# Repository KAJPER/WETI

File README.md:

# Bezkontaktowy miernik odległości (ultradźwiękowy)

Miernik odległości na mikrokontrolerze **ATtiny1616**, mierzący dystans do obiektu
ultradźwiękami **40 kHz** w zakresie **10–50 cm**. Projekt na ogólnopolski konkurs
**„Wygraj Indeks WETI 2026"** (Politechnika Gdańska).

Metoda hybrydowa **Pulse-Phase Ranging**: zgrubny pomiar czasu przelotu (ToF) z obwiedni
echa + docinanie fazą nośnej (filtr Goertzela), z kompensacją temperatury termistorem NTC.
Firmware napisany **w czystym AVR-GCC, na rejestrach (bez Arduino)**.

## Parametry (zmierzone)

| Parametr | Wartość |
|---|---|
| Zakres pomiaru | 10–50 cm (karton 20×20 cm) |
| Błąd RMSE | **≈ 2,4 mm** (35 odczytów, kalibracja liniowa) |
| Pobór mocy (spoczynek) | **0,18 mA @ 5 V = 0,9 mW** |
| Koszt elementów | 43,73 PLN |
| Zasilanie | 5 V (LDO MCP1700 → 3,3 V) |
| Zegar | 10 MHz (wewn. OSC20M / 2) |

## Jak to działa

1. **Nadawanie** — mikrokontroler generuje paczkę 40 kHz (dokładny rezonans przetwornika)
   na pinie PB0, wzmacnianą tranzystorem BC817.
2. **Odbiór** — echo wzmacnia dwustopniowy tor na MCP6002 (filtr pasmowy ~40 kHz),
   bramkowany P-MOSFET-em (BSS84) dla oszczędności energii.
3. **ToF** — ADC szybko próbkuje obwiednię echa (8-bit, ~115 ksps); początek echa
   (*onset*, próg 40 % szczytu z interpolacją) daje czas przelotu mierzony licznikiem
   TCB0 (100 ns/takt). Seria 9 strzałów → mediana + odrzucanie outlierów (MAD).
4. **Faza** — filtr Goertzela na buforze próbek wyznacza fazę nośnej (uśrednianą po
   pingach, z miarą spójności PLV) do dociągnięcia wyniku do siatki λ/2 ≈ 4,3 mm.
5. **Temperatura** — NTC 10 kΩ (model Beta) koryguje prędkość dźwięku c(T) = 331,3 + 0,606·T.
6. **Energia** — między pomiarami MCU śpi w trybie Standby, budzony z RTC/PIT;
   tor analogowy zasilany tylko na czas pomiaru.

Dostępna jest też **2-punktowa kalibracja polowa** zapisywana w EEPROM (wejście:
przytrzymanie przycisku przy starcie).

## Struktura repozytorium

| Katalog / plik | Zawartość |
|---|---|
| `firmware/` | Kod źródłowy (`main.c`), plik wynikowy (`main.hex`), `Makefile` |
| `dokumentacja-etap2/` | Dokumentacja prototypu (LaTeX + PDF), zdjęcia w `foto/` |
| `dokumentacja-etap1/` | Projekt koncepcyjny (teza, schemat, PCB, symulacje LTspice) |
| `deliverables/` | Paczka konkursowa (firmware, CAD, Gerber) |
| `obudowa/` | Modele obudowy (druk 3D) |
| `WETI_Kacper_Popko_Etap2.zip` | Gotowa paczka do oddania |

## Budowanie i wgranie firmware

Wymagane: `avr-gcc`, `avrdude`, programator UPDI (np. SerialUPDI / CP2102 albo
Arduino z jtag2updi).

```bash
cd firmware
make
avrdude -c jtag2updi -p attiny1616 -P COMx -b 115200 -U flash:w:main.hex:i
```

Wynik pomiaru wychodzi przez USART (pin PB2, 115200 8N1):
```
#1 D=203mm (Dc=204 ph=240.5 plv=98 T=22.6C 9/9 pk=18)
```
`D` — odległość po fuzji fazowej, `Dc` — zgrubna (ToF), `ph` — faza, `plv` — spójność
fazy, `T` — temperatura, `pk` — amplituda echa.

## Sprzęt

ATtiny1616-SN · MCP6002 (wzmacniacz) · MCP1700 (LDO 3,3 V) · BC817 (driver TX) ·
BSS84 (bramkowanie toru) · NTC 10 kΩ · para przetworników US 40 kHz · PCB 2-warstwowe 41 × 54,25 mm.

## Autor

Kacper Popko — projekt konkursowy „Wygraj Indeks WETI 2026".

## Licencja

© 2026 Kacper Popko. Projekt (sprzęt, oprogramowanie, dokumentacja) jest
**open source** na licencji
**[CC BY-NC-SA 4.0](https://creativecommons.org/licenses/by-nc-sa/4.0/deed.pl)**:

- ✅ możesz **kopiować, używać i edytować / rozwijać** projekt,
- ✏️ przeróbki musisz udostępniać **na tej samej licencji** (SA),
- 👤 musisz **podać autora** (Kacper Popko) (BY),
- 🚫 **nie wolno wykorzystywać komercyjnie** — w tym sprzedawać urządzenia,
  płytek, oprogramowania ani odpłatnych usług (NC).

Szczegóły w pliku [`LICENSE`](LICENSE).

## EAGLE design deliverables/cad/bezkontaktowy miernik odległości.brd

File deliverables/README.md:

# WETI 2026 — Etap 2: paczka dla Komisji

Termin: **19.06.2026, 15:00**. Poniżej checklista wymaganych plików i co już jest gotowe.

## Wymagane elementy (z regulaminu Etapu 2)

| # | Element | Status | Lokalizacja |
|---|---------|--------|-------------|
| 1 | Prototyp urządzenia (fizyczny) | ✅ zbudowany, działa | — (sprzęt) |
| 2 | Pliki produkcyjne PCB — **Gerber** | ✅ dodane (zip, v17) | `gerber/` |
| 3 | Pliki źródłowe CAD — schemat + PCB | ✅ dodane (.sch + .brd) | `cad/` |
| 4 | Oprogramowanie — źródło + plik końcowy | ✅ gotowe | `firmware/` |
| 5 | Dokumentacja | ✅ gotowa | `../dokumentacja-etap2/` |

Gerber (zip) zawiera komplet warstw: copper top/bottom, soldermask, silkscreen,
solderpaste, profil (obrys), drill (.xln) oraz pliki PnP/assembly — gotowe do
produkcji. CAD: `bezkontaktowy_miernik_odległości.sch` + `...brd` (EAGLE).

## 2 + 3: Referencja eksportu (zrobione)

Poniższa instrukcja pozostaje jako referencja, gdyby trzeba było wygenerować
Gerbery ponownie po zmianie PCB.

### Skopiuj źródła CAD → `cad/`
- `WETI.sch` (schemat)
- `WETI.brd` (płytka)

### Wyeksportuj Gerber → `gerber/` (EAGLE: File → CAM Processor)
Użyj wbudowanego job `gerber_2-layer` (albo `gerb274x`) i wygeneruj warstwy:

| Plik | Warstwa EAGLE | Opis |
|------|---------------|------|
| `*.GTL` | Top | miedź górna |
| `*.GBL` | Bottom | miedź dolna |
| `*.GTS` | tStop | soldermask górny |
| `*.GBS` | bStop | soldermask dolny |
| `*.GTO` | tPlace + tNames | opis górny (silk) |
| `*.GBO` | bPlace + bNames | opis dolny (silk) |
| `*.GTP` | tCream | pasta górna (opcjonalnie) |
| `*.GKO` / `*.GML` | Dimension | obrys płytki |
| `*.TXT` / `*.XLN` | Drill (Excellon) | otwory |

Po eksporcie sprawdź wynik w darmowym wieweru Gerber (np. **gerbv** albo
**JLCPCB/Aisler online viewer**) — czy warstwy się pokrywają i obrys jest zamknięty.

## 4: Oprogramowanie — gotowe ✅

W katalogu `../firmware/`:
- `main.c` — kod źródłowy (AVR-GCC, rejestrowo, ATtiny1616)
- `main.hex` — plik wynikowy (Intel HEX) do wgrania
- `Makefile` — budowanie i programowanie

Budowanie i wgranie:
```
cd firmware
make
avrdude -c jtag2updi -p attiny1616 -P COM5 -b 115200 -U flash:w:main.hex:i
```
(lub `-c serialupdi` dla programatora SerialUPDI/CP2102)

## 5: Dokumentacja — gotowa ✅

`../dokumentacja-etap2/WETI_Kacper_Popko_Etap2.tex` (+ skompilowany `.pdf`).

## Przed wysłaniem — checklista końcowa
- [ ] `cad/WETI.sch` i `cad/WETI.brd` wgrane
- [ ] `gerber/` zawiera wszystkie warstwy + drill, sprawdzone w viewerze
- [ ] `firmware/main.hex` aktualny (po `make`)
- [ ] `dokumentacja-etap2/*.pdf` skompilowany
- [ ] zdjęcia/rendery prototypu dołączone

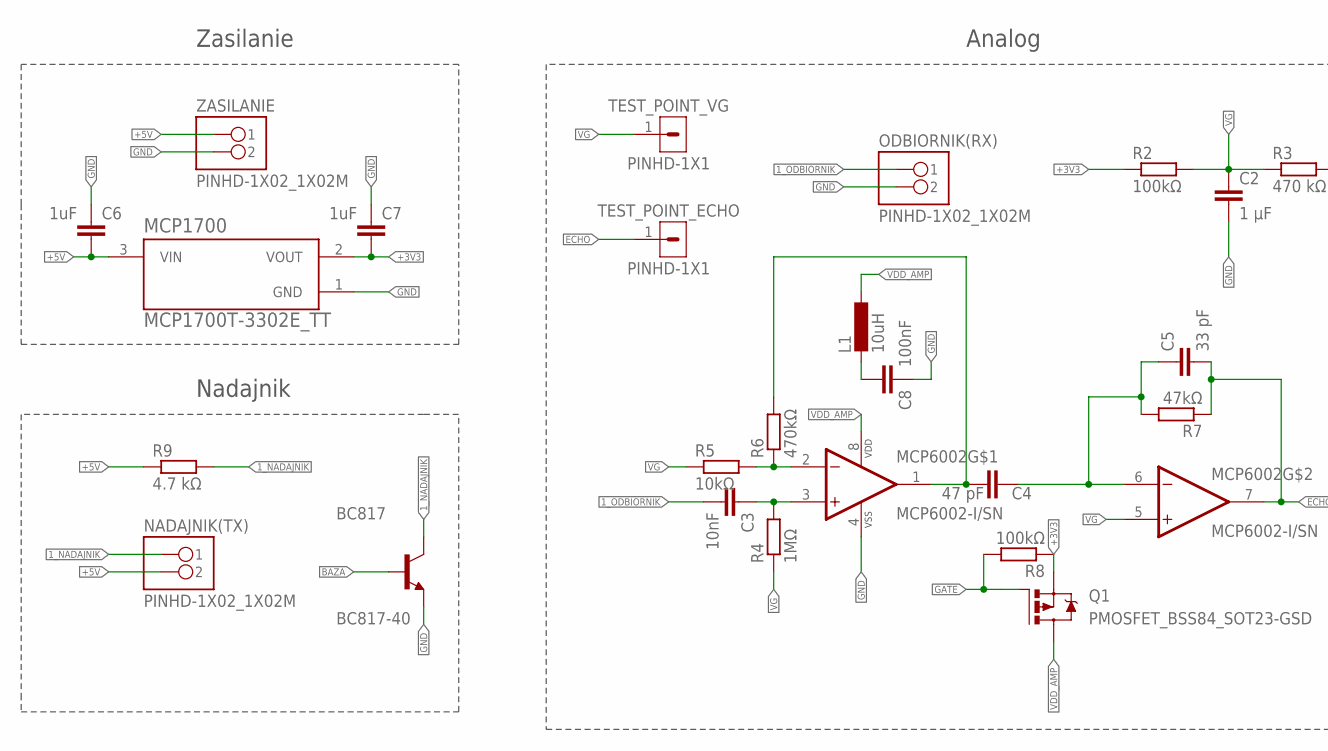
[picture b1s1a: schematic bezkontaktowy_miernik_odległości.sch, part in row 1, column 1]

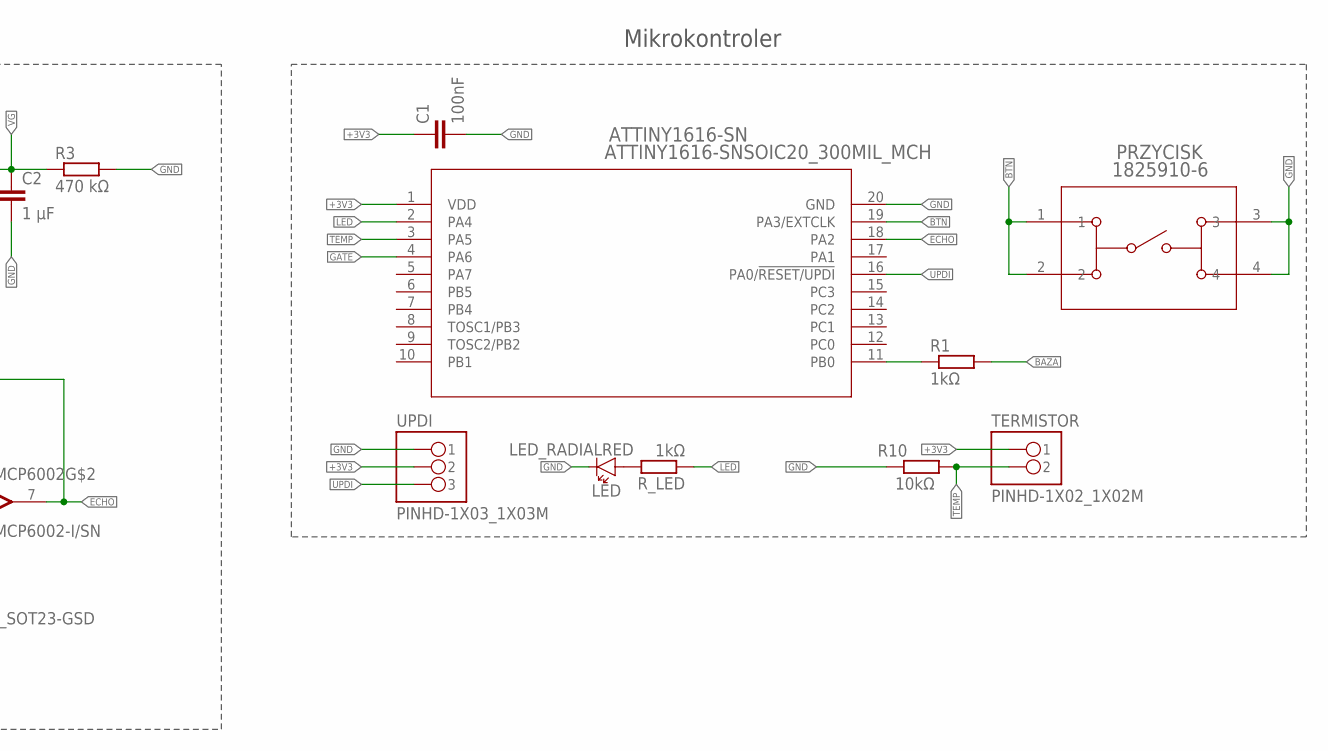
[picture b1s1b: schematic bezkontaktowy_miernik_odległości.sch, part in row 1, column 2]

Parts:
ATTINY1616-SN: ATTINY1616-SNSOIC20_300MIL_MCH; SOIC20_300MIL_MCH
BC817: BC817-40; SOT95P240X120-3N
C1, C8: 100nF; C0603
C2: 1 µF; C0603
C3: 10nF; C0603
C4: 47 pF; C0603
C5: 33 pF; C0603
C6, C7: 1uF; C0603
L1: 10uH; 0204/7
LED: LED_RADIALRED; LEDRD254W60D565H860B_R
MCP1700: MCP1700T-3302E_TT; SOT95P237X112-3N
MCP6002: MCP6002-I/SN; SOIC127P600X175-8N
NADAJNIK(TX): PINHD-1X02_1X02M; 1X02
ODBIORNIK(RX): PINHD-1X02_1X02M; 1X02
PRZYCISK: 1825910-6; SW4_1825910-B
Q1: PMOSFET_BSS84_SOT23-GSD; SOT23
R1: 1kΩ; R0603
R2, R8: 100kΩ; R0603
R3: 470 kΩ; R0603
R4: 1MΩ; R0603
R5, R10: 10kΩ; R0603
R6: 470kΩ; R0603
R7: 47kΩ; R0603
R9: 4.7 kΩ; R0603
R_LED: 1kΩ; R0603
TERMISTOR: PINHD-1X02_1X02M; 1X02
TEST_POINT_ECHO: PINHD-1X1; 1X01
TEST_POINT_VG: PINHD-1X1; 1X01
UPDI: PINHD-1X03_1X03M; 1X03
ZASILANIE: PINHD-1X02_1X02M; 1X02

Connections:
1_NADAJNIK: BC817.3 (C), NADAJNIK(TX).1, R9.2
1_ODBIORNIK: C3.2, ODBIORNIK(RX).1
+3V3: ATTINY1616-SN.1 (VDD), C1.1, C7.2, MCP1700.2 (VOUT), Q1.2 (S), R2.1, R8.1, TERMISTOR.1, UPDI.2
+5V: C6.2, MCP1700.3 (VIN), NADAJNIK(TX).2, R9.1, ZASILANIE.1
BAZA: BC817.1 (B), R1.2
BTN: ATTINY1616-SN.19 (PA3/EXTCLK), PRZYCISK.1, PRZYCISK.2
ECHO: ATTINY1616-SN.18 (PA2), C5.2, MCP6002.7 (VOUTB), R7.1, TEST_POINT_ECHO.1
GATE: ATTINY1616-SN.4 (PA6), Q1.1 (G), R8.2
GND: ATTINY1616-SN.20 (GND), BC817.2 (E), C1.2, C2.2, C6.1, C7.1, C8.1, LED.C, MCP1700.1 (GND), MCP6002.4 (VSS), ODBIORNIK(RX).2, PRZYCISK.3, PRZYCISK.4, R3.2, R10.1, UPDI.1, ZASILANIE.2
LED: ATTINY1616-SN.2 (PA4), R_LED.1
unnamed: C3.1, MCP6002.3 (VINA+), R4.2
unnamed: MCP6002.2 (VINA-), R5.2, R6.1
unnamed: C4.2, MCP6002.1 (VOUTA), R6.2
unnamed: LED.A, R_LED.2
unnamed: C4.1, C5.1, MCP6002.6 (VINB-), R7.2
unnamed: C8.2, L1.2
unnamed: ATTINY1616-SN.11 (PB0), R1.1
TEMP: ATTINY1616-SN.3 (PA5), R10.2, TERMISTOR.2
UPDI: ATTINY1616-SN.16 (PA0/!RESET/UPDI), UPDI.3
VDD_AMP: L1.1, MCP6002.8 (VDD), Q1.3 (D)
VG: C2.1, MCP6002.5 (VINB+), R2.2, R3.1, R4.1, R5.1, TEST_POINT_VG.1

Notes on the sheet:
Zasilanie
Nadajnik
Analog
Mikrokontroler

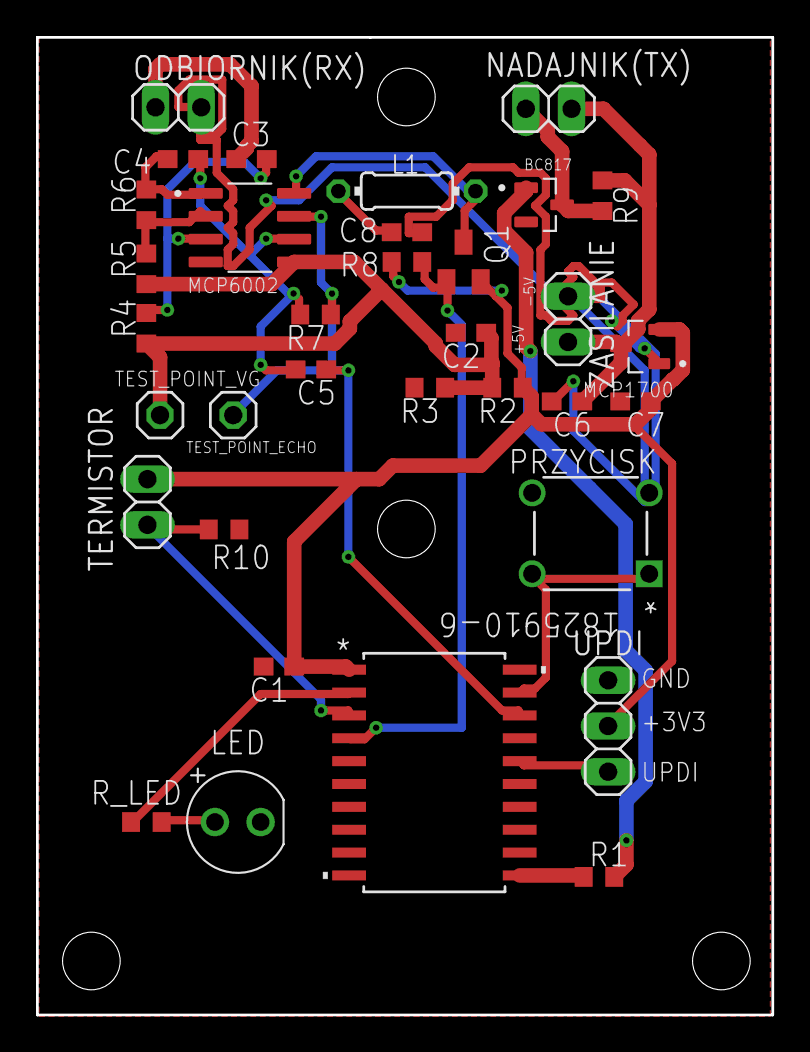
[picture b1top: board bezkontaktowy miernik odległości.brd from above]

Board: 2 copper layers, 40.9 x 54.3 mm, 34 parts (0 on the bottom side), 21 nets.

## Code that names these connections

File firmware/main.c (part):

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 * ATtiny1616 ultrasonic distance meter — v2 hardware echo capture.
 *
 * Pinout (after PCB mod):
 *   PA0  UPDI
 *   PA1  -                (free, was wrongly assumed ECHO earlier)
 *   PA2  -                (free, was ADC ECHO before PCB mod)
 *   PA3  BTN              (pull-up, active LOW, BOTHEDGES wake)
 *   PA4  LED              (active HIGH)
 *   PA5  TEMP NTC         (ADC0 AIN5)
 *   PA6  GATE Q1          (LOW = Q1 ON = op-amp powered)
 *   PB0  BAZA TX          (40 kHz software bitbang)
 *   PB2  USART0 TXD       (115200 8N1)
 *   PB4  ECHO             (AC1 AINP3 — hardware capture path)
 *
 * Detection chain (zero CPU latency):
 *   echo → op-amp → PB4 → AC1 (vs DAC1 threshold) → EVSYS → TCB0.CAPT
 *   NOTE: PB4 is AINP3 on AC1 (positive); on AC0 it is AINN1 (negative).
 * TCB0 latches CCMP exactly when AC0 toggles, no software loop needed.
 * 1 tick @ F_CPU=10 MHz = 100 ns; 16-bit counter = max 6.55 ms = 1.12 m.
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/* ============================== GPIO ================================== */
static void gpio_init(void)
{
    /* PA3 button with pull-up + BOTHEDGES IRQ (IDLE wake) */
    PORTA.DIRCLR   = PIN3_bm;
    PORTA.PIN3CTRL = PORT_PULLUPEN_bm | PORT_ISC_BOTHEDGES_gc;

    /* PA4 LED */
    PORTA.DIRSET = PIN4_bm; PORTA.OUTCLR = PIN4_bm;

    /* PA5 NTC analog input */
    PORTA.DIRCLR   = PIN5_bm;
    PORTA.PIN5CTRL = PORT_ISC_INPUT_DISABLE_gc;

    /* PA6 GATE Q1 — DIAGNOSTIC: Q1 ALWAYS ON so PB4 can be measured stably */
    PORTA.DIRSET = PIN6_bm; PORTA.OUTCLR = PIN6_bm;

    /* PB0 TX burst output */
    PORTB.DIRSET = PIN0_bm; PORTB.OUTCLR = PIN0_bm;

    /* PB2 USART TX */
    PORTB.DIRSET = PIN2_bm; PORTB.OUTSET = PIN2_bm;

    /* PB4 ECHO input for AC0 — disable digital, no pull */
    PORTB.DIRCLR   = PIN4_bm;
    PORTB.PIN4CTRL = PORT_ISC_INPUT_DISABLE_gc;

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}

/* ============================== NTC =================================== */
/* Topology: +3V3 -- NTC -- PA5 -- R10(10k) -- GND */
static int16_t ntc_read_temp_c16(void)
{
    uint16_t a = adc_read(ADC_MUXPOS_AIN5_gc);
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/* ============================== AC0 + DAC0 ============================ */
/* DAC0 generates threshold internally (no pin output).
 * CRITICAL (verified datasheet Table 5-1): on AC0, PB4 = AINN1 (NEGATIVE);
 * PB4 = AINP3 (positive) ONLY on AC1. So we MUST use AC1 for echo on PB4.
 * Datasheet 29.x: "AC1 uses DAC1" — threshold comes from DAC1, ref via
 * VREF.CTRLC (DAC1REFSEL) + VREF.CTRLB (DAC1REFEN, bit3).
 * AC1 compares PB4 (AINP3) vs DAC1; AC1_OUT → EVSYS → TCB0 capture. */
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
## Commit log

2026-05-13 Add initial firmware binary for test_pb0
    This commit introduces the firmware binary file `test_pb0.hex`, which contains the necessary machine code for the initial testing phase. The hex file includes a series of instructions and data requir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
2026-06-09 Add initial documentation for stage 1 in PDF format
2026-06-11 Add ESP32 power monitor and I2C scanner sketches
    - Implemented a power monitor for the WETI ultrasonic distance meter using INA219, featuring a web dashboard for live current, voltage, and power readings.
    - Added an I2C scanner sketch to identify connected I2C devices and their addresses.
2026-06-11 Add documentation for Stage 2 of the ultrasonic distance meter project
    - Created a new LaTeX document for Stage 2 documentation detailing the prototype's design, architecture, and performance.
    - Included sections on the introduction, requirements fulfillment, device architecture, firmware details, power management, measurement results, changes from Stage 1, deliverables, and future develop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
    - Added a table of contents for easy navigation within the document.
2026-06-11 Refactor code structure for improved readability and maintainability
2026-06-13 Add measurement characteristics and residual analysis plots to documentation
    - Included a new figure displaying the measurement characteristics after calibration, showing the correlation between actual distance and readings with a high R² value.
    - Added a second figure illustrating the residuals of the measurements compared to the reference, including error margins.
    - Updated LaTeX document to incorporate the new plots using the pgfplots package for enhanced visualization.
    Update firmware map file with new temporary object file references
    - Replaced references to temporary object files in the firmware map with updated file names.
    - Ensured consistency in the linker script and memory map b
2026-06-14 Add .gitignore, LICENSE, and README files for project documentation and licensing
2026-06-23 Add presentation notes for WETI 2026 on ultrasonic distance measurement project

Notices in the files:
parts and their libraries:
COPYRIGHT: Copyright (C) 2025 Ultra Librarian. All rights reserved.
COPYRIGHT: Copyright (C) 2016 Accelerated Designs. All rights reserved
